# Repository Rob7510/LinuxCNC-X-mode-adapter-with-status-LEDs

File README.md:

# LinuxCNC signal adapter for a parallel port operating in X-mode.
**Version 153-06A**

This is the same design as the X-mode printer port adapter 153-01, with two LED arrays added that indicate the status of Pins 2-9 and 10-17. Pin 1 has its own LED.# LinuxCNC-X-mode-adapter-with-status-LEDs

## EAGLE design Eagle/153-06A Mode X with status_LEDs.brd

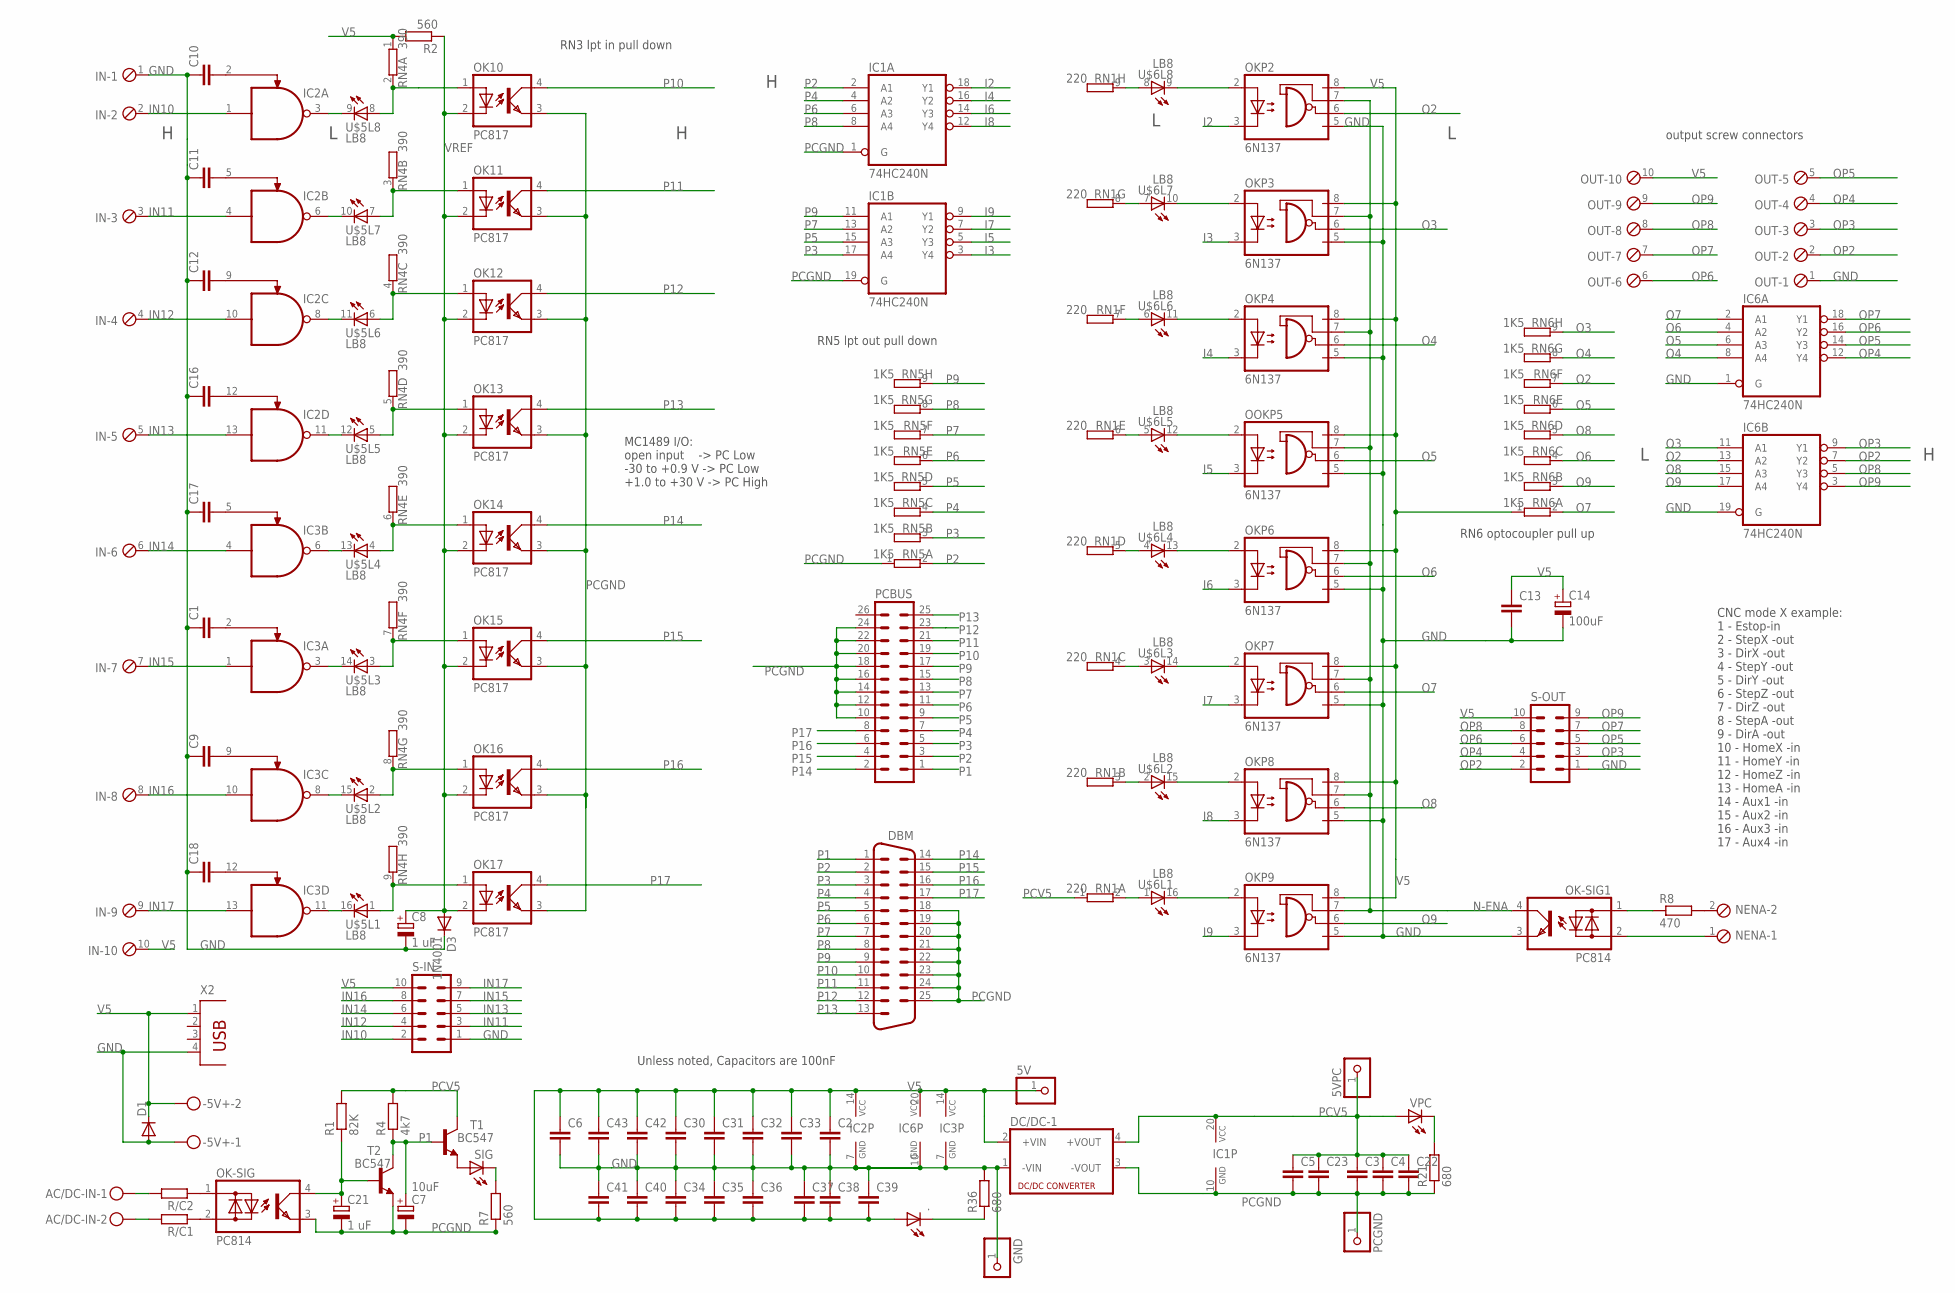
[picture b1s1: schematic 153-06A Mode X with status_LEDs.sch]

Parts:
5V, 5VPC: PINHD-1X1; 1X01
-5V+: MKDSN1,5/2-5,08
.: LED3MM
AC/DC-IN: MKDSN1,5/2-5,08
C1, C2, C3, C4, C5, C6, C9, C10, C11, C12, C13, C16, C17, C18, C22, C23, C30, C31, C32, C33, C34, C35, C36, C37, C38, C39, C40, C41, C42, C43: C-EU025-024X044; C025-024X044
C7: 10uF; E5-6
C8, C21: 1 uF; E2,5-6
C14: 100uF; E3,5-8
D1: 1N4148DO35-10; DO35-10
D3: 1N4001; DO35-10
DBM: M25HP
DC/DC-1: VA-1205S; 4SIL
GND: PINHD-1X1; 1X01
IC1, IC6: 74HC240N; DIL20
IC2, IC3: MC1489DIP; DIL14
IN: MPT10; 10POL254
NENA: MPT2; 2POL254
OK10, OK11, OK12, OK13, OK14, OK15, OK16, OK17: PC817; DIL04
OK-SIG, OK-SIG1: PC814; DIL04
OKP2, OKP3, OKP4, OKP6, OKP7, OKP8, OKP9: 6N137; DIL08
OOKP5: 6N137; DIL08
OUT: MPT10; 10POL254
PCBUS: ML26
PCGND: PINHD-1X1; 1X01
R1: 82K; 0207/10
R2, R7: 560; 0207/10
R4: 4k7; 0207/10
R8: 470; 0207/10
R21, R36: 680; 0207/10
R/C1, R/C2: R-EU_0309/10; 0309/10
RN1: 220; SIL9
RN4: 390; SIL9
RN5, RN6: 1K5; SIL9
S-IN: ML10
S-OUT: ML10
SIG: LED3MM
T1, T2: BC547; TO92
U$5, U$6: LB8
VPC: LED3MM
X2: PN87520

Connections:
GND: -5V+.1, C1.1, C2.2, C6.2, C8.-, C9.1, C10.1, C11.1, C12.1, C13.2, C14.-, C16.1, C17.1, C18.1, C30.2, C31.2, C32.2, C33.2, C34.1, C35.1, C36.1, C37.1, C38.1, C39.1, C40.1, C41.1, C42.2, C43.2, D1.A, D3.C, DC/DC-1.1 (-VIN), GND.1, IC2.7 (GND), IC3.7 (GND), IC6.1 (G), IC6.10 (GND), IC6.19 (G), IN.1, OK-SIG1.3 (E), OKP2.5 (GND), OKP3.5 (GND), OKP4.5 (GND), OKP6.5 (GND), OKP7.5 (GND), OKP8.5 (GND), OKP9.5 (GND), OOKP5.5 (GND), OUT.1, R36.2, S-IN.1, S-OUT.1, X2.4
I2: IC1.18 (Y1), OKP2.3 (C)
I3: IC1.3 (Y4), OKP3.3 (C)
I4: IC1.16 (Y2), OKP4.3 (C)
I5: IC1.5 (Y3), OOKP5.3 (C)
I6: IC1.14 (Y3), OKP6.3 (C)
I7: IC1.7 (Y2), OKP7.3 (C)
I8: IC1.12 (Y4), OKP8.3 (C)
I9: IC1.9 (Y1), OKP9.3 (C)
IN10: IC2.1 (I0), IN.2, S-IN.2
IN11: IC2.4 (I0), IN.3, S-IN.3
IN12: IC2.10 (I0), IN.4, S-IN.4
IN13: IC2.13 (I0), IN.5, S-IN.5
IN14: IC3.4 (I0), IN.6, S-IN.6
IN15: IC3.1 (I0), IN.7, S-IN.7
IN16: IC3.10 (I0), IN.8, S-IN.8
IN17: IC3.13 (I0), IN.9, S-IN.9
unnamed: RN1.2, U$6.1 (A)
unnamed: IC3.11 (O), U$5.16 (C)
unnamed: C10.2, IC2.2 (I1)
unnamed: R21.2, VPC.K (C)
unnamed: C17.2, IC3.5 (I1)
unnamed: OK10.1 (A), RN4.2, U$5.8 (A)
unnamed: OKP9.2 (A), U$6.16 (C)
unnamed: OK11.1 (A), RN4.3 (2), U$5.7 (A)
unnamed: OK12.1 (A), RN4.4 (2), U$5.6 (A)
unnamed: C1.2, IC3.2 (I1)
unnamed: C9.2, IC3.9 (I1)
unnamed: C18.2, IC3.12 (I1)
unnamed: IC2.3 (O), U$5.9 (C)
unnamed: IC2.6 (O), U$5.10 (C)
unnamed: OK13.1 (A), RN4.5 (2), U$5.5 (A)
unnamed: OK14.1 (A), RN4.6 (2), U$5.4 (A)
unnamed: OK15.1 (A), RN4.7 (2), U$5.3 (A)
unnamed: OK16.1 (A), RN4.8 (2), U$5.2 (A)
unnamed: OK-SIG.1 (AC1), R/C2.1
unnamed: OK-SIG.2 (AC2), R/C1.1
unnamed: OK17.1 (A), RN4.9 (2), U$5.1 (A)
unnamed: AC/DC-IN.2, R/C1.2
unnamed: AC/DC-IN.1, R/C2.2
unnamed: RN1.3 (2), U$6.2 (A)
unnamed: RN1.4 (2), U$6.3 (A)
unnamed: OKP7.2 (A), U$6.14 (C)
unnamed: OKP8.2 (A), U$6.15 (C)
unnamed: RN1.5 (2), U$6.4 (A)
unnamed: C21.+, OK-SIG.4 (C), R1.1, T2.2 (B)
unnamed: OKP6.2 (A), U$6.13 (C)
unnamed: ..K (C), R36.1
unnamed: IC3.8 (O), U$5.15 (C)
unnamed: IC3.3 (O), U$5.14 (C)
unnamed: IC3.6 (O), U$5.13 (C)
unnamed: C11.2, IC2.5 (I1)
unnamed: C12.2, IC2.9 (I1)
unnamed: C16.2, IC2.12 (I1)
unnamed: IC2.8 (O), U$5.11 (C)
unnamed: IC2.11 (O), U$5.12 (C)
unnamed: RN1.6 (2), U$6.5 (A)
unnamed: OOKP5.2 (A), U$6.12 (C)
unnamed: RN1.7 (2), U$6.6 (A)
unnamed: OKP4.2 (A), U$6.11 (C)
unnamed: OK-SIG1.1 (AC1), R8.1
unnamed: RN1.8 (2), U$6.7 (A)
unnamed: OKP3.2 (A), U$6.10 (C)
unnamed: RN1.9 (2), U$6.8 (A)
unnamed: OKP2.2 (A), U$6.9 (C)
unnamed: R7.2, SIG.K (C)
unnamed: SIG.A, T1.1 (E)
unnamed: NENA.2, R8.2
unnamed: NENA.1, OK-SIG1.2 (AC2)
N-ENA: OK-SIG1.4 (C), OKP2.7 (VE), OKP3.7 (VE), OKP4.7 (VE), OKP6.7 (VE), OKP7.7 (VE), OKP8.7 (VE), OKP9.7 (VE), OOKP5.7 (VE)
O2: IC6.13 (A2), OKP2.6 (VO), RN6.7 (2)
O3: IC6.11 (A1), OKP3.6 (VO), RN6.9 (2)
O4: IC6.8 (A4), OKP4.6 (VO), RN6.8 (2)
O5: IC6.6 (A3), OOKP5.6 (VO), RN6.6 (2)
O6: IC6.4 (A2), OKP6.6 (VO), RN6.4 (2)
O7: IC6.2 (A1), OKP7.6 (VO), RN6.2
O8: IC6.15 (A3), OKP8.6 (VO), RN6.5 (2)
O9: IC6.17 (A4), OKP9.6 (VO), RN6.3 (2)
OP2: IC6.7 (Y2), OUT.2, S-OUT.2
OP3: IC6.9 (Y1), OUT.3, S-OUT.3
OP4: IC6.12 (Y4), OUT.4, S-OUT.4
OP5: IC6.14 (Y3), OUT.5, S-OUT.5
OP6: IC6.16 (Y2), OUT.6, S-OUT.6
OP7: IC6.18 (Y1), OUT.7, S-OUT.7
OP8: IC6.5 (Y3), OUT.8, S-OUT.8
OP9: IC6.3 (Y4), OUT.9, S-OUT.9
P1: C7.+, DBM.1, PCBUS.1, R4.1, T1.2 (B), T2.3 (C)
P2: DBM.2, IC1.2 (A1), PCBUS.3, RN5.2
P3: DBM.3, IC1.17 (A4), PCBUS.5, RN5.3 (2)
P4: DBM.4, IC1.4 (A2), PCBUS.7, RN5.4 (2)
P5: DBM.5, IC1.15 (A3), PCBUS.9, RN5.5 (2)
P6: DBM.6, IC1.6 (A3), PCBUS.11, RN5.6 (2)
P7: DBM.7, IC1.13 (A2), PCBUS.13, RN5.7 (2)
P8: DBM.8, IC1.8 (A4), PCBUS.15, RN5.8 (2)
P9: DBM.9, IC1.11 (A1), PCBUS.17, RN5.9 (2)
P10: DBM.10, OK10.4 (COL), PCBUS.19
P11: DBM.11, OK11.4 (COL), PCBUS.21
P12: DBM.12, OK12.4 (COL), PCBUS.23
P13: DBM.13, OK13.4 (COL), PCBUS.25
P14: DBM.14, OK14.4 (COL), PCBUS.2
P15: DBM.15, OK15.4 (COL), PCBUS.4
P16: DBM.16, OK16.4 (COL), PCBUS.6
P17: DBM.17, OK17.4 (COL), PCBUS.8
PCGND: C3.2, C4.2, C5.2, C7.-, C21.-, C22.2, C23.2, DBM.18, DBM.19, DBM.20, DBM.21, DBM.22, DBM.23, DBM.24, DBM.25, DC/DC-1.3 (-VOUT), IC1.1 (G), IC1.10 (GND), IC1.19 (G), OK10.3 (EMIT), OK11.3 (EMIT), OK12.3 (EMIT), OK13.3 (EMIT), OK14.3 (EMIT), OK15.3 (EMIT), OK16.3 (EMIT), OK17.3 (EMIT), OK-SIG.3 (E), PCBUS.10, PCBUS.12, PCBUS.14, PCBUS.16, PCBUS.18, PCBUS.20, PCBUS.22, PCBUS.24, PCGND.1, R7.1, R21.1, RN5.1, T2.1 (E)
PCV5: 5VPC.1, C3.1, C4.1, C5.1, C22.1, C23.1, DC/DC-1.4 (+VOUT), IC1.20 (VCC), R1.2, R4.2, RN1.1, T1.3 (C), VPC.A
V5: 5V.1, -5V+.2, ..A, C2.1, C6.1, C13.1, C14.+, C30.1, C31.1, C32.1, C33.1, C34.2, C35.2, C36.2, C37.2, C38.2, C39.2, C40.2, C41.2, C42.1, C43.1, D1.C, DC/DC-1.2 (+VIN), IC2.14 (VCC), IC3.14 (VCC), IC6.20 (VCC), IN.10, OKP2.8 (VCC), OKP3.8 (VCC), OKP4.8 (VCC), OKP6.8 (VCC), OKP7.8 (VCC), OKP8.8 (VCC), OKP9.8 (VCC), OOKP5.8 (VCC), OUT.10, R2.2, RN4.1, RN6.1, S-IN.10, S-OUT.10, X2.1
VREF: C8.+, D3.A, OK10.2 (C), OK11.2 (C), OK12.2 (C), OK13.2 (C), OK14.2 (C), OK15.2 (C), OK16.2 (C), OK17.2 (C), R2.1

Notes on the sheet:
CNC mode X example: 1 - Estop-in 2 - StepX -out 3 - DirX -out 4 - StepY -out 5 - DirY -out 6 - StepZ -out 7 - DirZ -out 8 - StepA -out 9 - DirA -out 10 - HomeX -in 11 - HomeY -in 12 - HomeZ -in 13 - HomeA -in 14 - Aux1 -in 15 - Aux2 -in 16 - Aux3 -in 17 - Aux4 -in
MC1489 I/O: open input -> PC Low -30 to +0.9 V -> PC Low +1.0 to +30 V -> PC High
RN5 lpt out pull down
RN3 lpt in pull down
RN6 optocoupler pull up
output screw connectors
Unless noted, Capacitors are 100nF

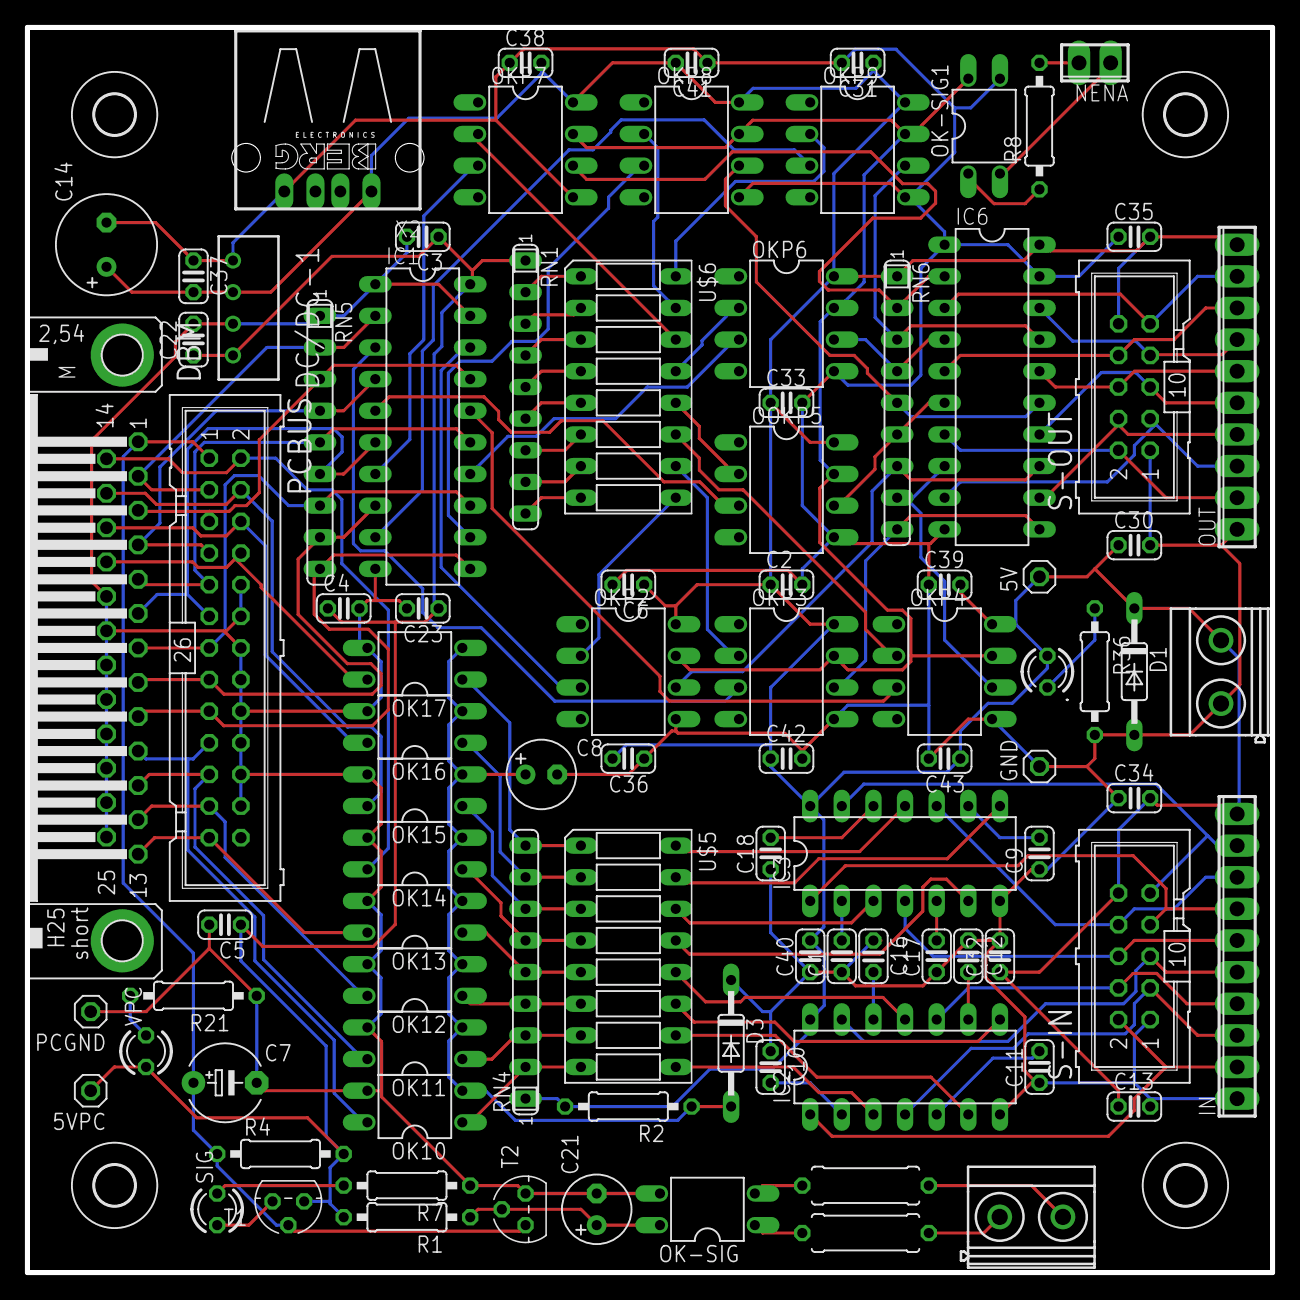
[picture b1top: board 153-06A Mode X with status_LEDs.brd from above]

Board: 2 copper layers, 100.0 x 100.0 mm, 97 parts (0 on the bottom side), 107 nets.

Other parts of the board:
U$1, U$2, U$3, U$4: 3,2

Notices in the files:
Eagle/153-06A Mode X with status_LEDs.brd:
License CERN-OHL-P V2
